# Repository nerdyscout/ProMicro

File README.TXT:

# ProMicro

## PCBs
collection of various PCBs stackable onto various MCU modules like
- [Sparkfun ProMicro](https://www.sparkfun.com/products/12587)
- [Arduino ProMini](https://store.arduino.cc/arduino-pro-mini)
- [Pro Mini nRF52](https://www.tindie.com/products/prominimicros/pro-mini-nrf52-nordic-nrf52832/)

:warning: all modules run with 3.3V, some might be 5V tolerant, but it is up to you to verify!

| PCB | Build | Status | Description |
| --- | --- | --- | --- |
| [ANA](ANA/README.TXT) |  | draft | 2ch analog in/out |
| [BOOST](BOOST) |  | prototype | Lipo battery charger |
| [BUS](BUS/README.TXT) |  | prototype | Modbus and CANbus module |
| [CONN](CONN/README.TXT) |  | prototype | CONN |
| [ESP](ESP) |  | draft | ESP |
| [LOG](LOG/README.TXT) |  | prototype | micro SD card shield with real time clock |
| [LORA](LORA/README.TXT) |  | prototype | Lora transceiver 868MHz |
| [POS](POS/README.TXT) |  | prototype | GPS receiver and gyroscope module |
| [QWIIC](QWIIC/README.TXT) |  | draft | BME280 sensor and analog extension |
| [UART](UART/README.TXT) |  | prototype | USB to RS232, RS485, SPI, I2C, JTAG |
| [WING](WING/README.TXT) |  | draft | Adafruit FeatherWing Breakout |
| [ZPM](ZPM/README.TXT) |  | draft | energy harvesting module |

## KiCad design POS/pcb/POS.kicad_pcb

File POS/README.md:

# ProMicro_POS 
This module can be mounted to an [Arduino Pro Mini](https://www.sparkfun.com/products/11113), [Arduino Nano](https://store.arduino.cc/arduino-nano), [Sparkfun Pro Micro](https://www.sparkfun.com/products/12587), or any other pincompatible MCU running with 3.3V. Depending on assembly it provides GPS and/or GYRO data. Manufacturing this PCB with 0.8mm thickness allows to mount a [LORA](../LORA) module onto its back.

## Documentation 
All files can be found on [Github](https://github.com/nerdyscout/ProMicro/tree/master/POS).

### Schematic

### BoM
  * [interactiveHTMLBoM](https://nerdyscout.github.io/ProMicro/POS/docs/bom/POS-ibom.html)
  * [octopart](pcb/docs/bom/POS-bom_octopart.csv)

## Hardware 
### Layout

### Gerbers
can be found within the Github [repository](pcb/gerbers).

## Code  (unless otherwise stated)
  * GPS
    * [Arduino Nano](examples/Arduino_Nano_GPS/Arduino_Nano_GPS.ino)
    * [Sparkfun ProMicro](examples/Sparkfun_GPS/Sparkfun_GPS.ino)
  * GYRO
    * [ICM20948](examples/Sparkfun_ICM20948/Sparkfun_ICM20948.ino)
    * [MPU9250](examples/Sparkfun_MPU9250/Sparkfun_MPU9250.ino)

## external
### Links
  * [hackaday.io](https://hackaday.io/project/171898-promicro)

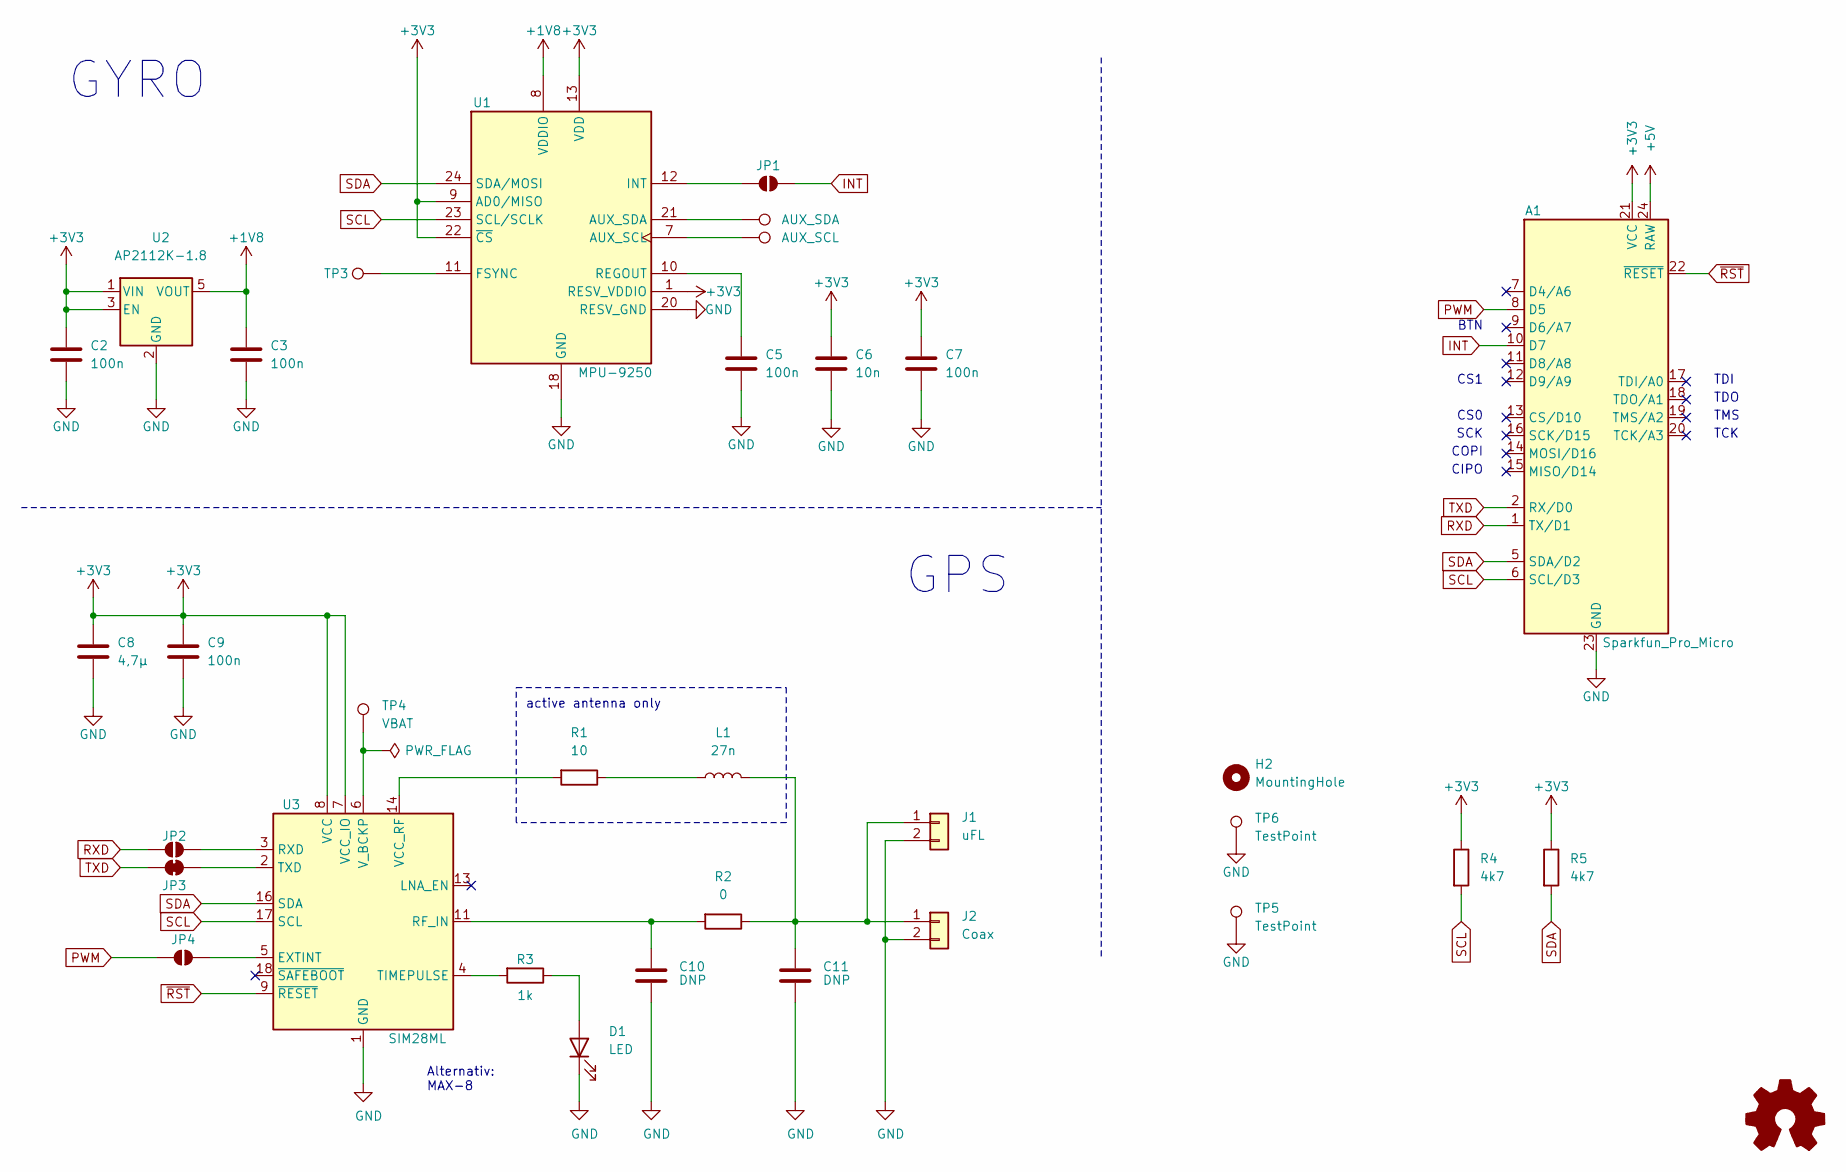
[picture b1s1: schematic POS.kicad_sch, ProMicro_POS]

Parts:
A1: Sparkfun_Pro_Micro
C2, C3, C5, C7, C9: 100n; C_0603_1608Metric; MPN CL05B104KO5NNNC; LCSC# C1525
C6: 10n; C_0603_1608Metric; MPN CL05B103KB5NNNC; LCSC# C15195
C8: 4,7µ; C_0603_1608Metric; MPN CL10A475KO8NNNC; LCSC# C19666
C10, C11: DNP; C_0603_1608Metric
D1: LED; LED_0603_1608Metric; MPN 19-217/BHC-ZL1M2RY/3T; LCSC# C72041
H2: MountingHole; MountingHole_2.1mm
J1: uFL; U.FL_Hirose_U.FL-R-SMT-1_Vertical
J2: Coax; SMA_Samtec_SMA-J-P-H-ST-EM1_EdgeMount
JP1, JP4: SolderJumper_2_Open; SolderJumper-2_P1.3mm_Open_RoundedPad1.0x1.5mm
JP2: Jumper_NO_Small; SolderJumper-2_P1.3mm_Open_RoundedPad1.0x1.5mm
JP3: Jumper_NC_Small; SolderJumper-2_P1.3mm_Bridged_RoundedPad1.0x1.5mm
L1: 27n; L_0603_1608Metric
LOGO1: Logo_Open_Hardware_Small; OSHW-Symbol_6.7x6mm_SilkScreen
R1: 10; R_0603_1608Metric
R2: 0; R_0603_1608Metric; MPN 0402WGF0000TCE; LCSC# C17168
R3: 1k; R_0603_1608Metric; MPN 0402WGF1001TCE; LCSC# C11702
R4, R5: 4k7; R_0603_1608Metric; MPN 0402WGF4701TCE; LCSC# C25900
TP1: AUX_SDA; TestPoint_Pad_D1.5mm
TP2: AUX_SCL; TestPoint_Pad_D1.5mm
TP3: FSYNC; TestPoint_Pad_D1.5mm
TP4: VBAT; TestPoint_THTPad_D1.5mm_Drill0.7mm
TP5, TP6: TestPoint; TestPoint_Pad_1.5x1.5mm
U1: MPU-9250; InvenSense_QFN-24_3x3mm_P0.4mm; MPN MPU-9250; LCSC# C71459
U2: AP2112K-1.8; SOT-23-5
U3: SIM28ML; ublox_MAX; MPN MAX-8C-0-10

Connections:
+1V8: C3.1, U1.8 (VDDIO), U2.5 (VOUT)
+3V3: A1.21 (VCC), C2.1, C6.1, C7.1, C8.1, C9.1, R4.1, R5.1, U1.1 (RESV_VDDIO), U1.9 (AD0/MISO), U1.13 (VDD), U1.22 (~CS), U2.1 (VIN), U2.3 (EN), U3.7 (VCC_IO), U3.8 (VCC)
+5V: A1.24 (RAW)
GND: A1.3 (GND), A1.4 (GND), A1.23 (GND), C2.2, C3.2, C5.2, C6.2, C7.2, C8.2, C9.2, C10.2, C11.2, D1.1 (K), J1.2, J2.2, TP5.1, TP6.1, U1.18 (GND), U1.20 (RESV_GND), U2.2 (GND), U3.1 (GND), U3.10 (GND), U3.12 (GND)
INT: A1.10 (D7), JP1.2 (B)
unnamed: C5.1, U1.10 (REGOUT)
unnamed: C10.1, R2.2, U3.11 (RF_IN)
unnamed: C11.1, J1.1, J2.1, L1.2, R2.1
unnamed: D1.2 (A), R3.1
unnamed: JP1.1 (A), U1.12 (INT)
unnamed: JP2.1 (A), U3.3 (RXD)
unnamed: JP3.1 (A), U3.2 (TXD)
unnamed: JP4.2 (B), U3.5 (EXTINT)
unnamed: L1.1, R1.1
unnamed: R1.2, U3.14 (VCC_RF)
unnamed: R3.2, U3.4 (TIMEPULSE)
unnamed: TP1.1, U1.21 (AUX_SDA)
unnamed: TP2.1, U1.7 (AUX_SCL)
unnamed: TP3.1, U1.11 (FSYNC)
unnamed: TP4.1, U3.6 (V_BCKP)
PWM: A1.8 (D5), JP4.1 (A)
RXD: A1.1 (TX/D1), JP2.2 (B)
SCL: A1.6 (SCL/D3), R4.2, U1.23 (SCL/SCLK), U3.17 (SCL)
SDA: A1.5 (SDA/D2), R5.2, U1.24 (SDA/MOSI), U3.16 (SDA)
TXD: A1.2 (RX/D0), JP3.2 (B)
~RST: A1.22 (~RESET), U3.9 (~RESET)

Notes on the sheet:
TMS
CIPO
CS1
TDI
GPS
TDO
BTN
GYRO
SCK
CS0
Alternativ: MAX-8
TCK
active antenna only
COPI

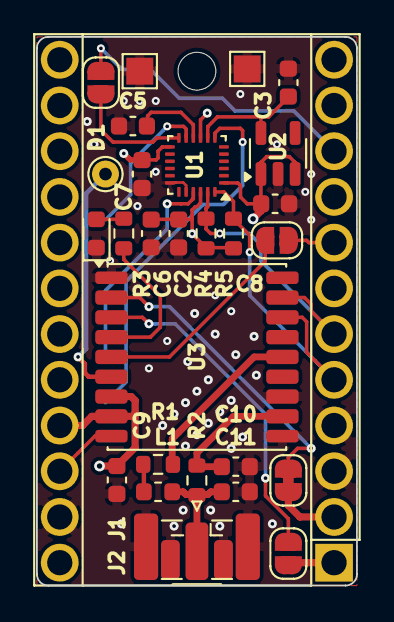
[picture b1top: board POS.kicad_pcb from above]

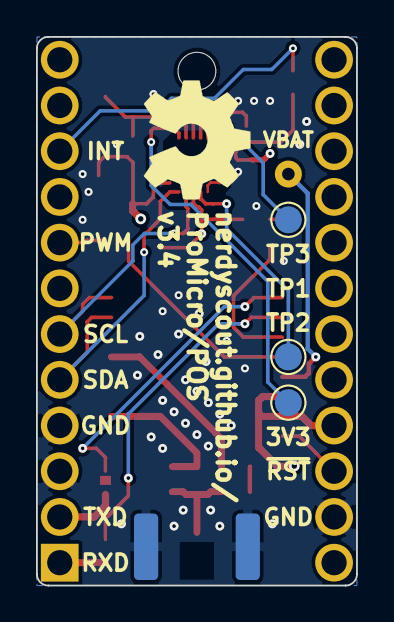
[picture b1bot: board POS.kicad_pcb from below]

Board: 4 copper layers, 17.8 x 30.5 mm, 34 parts (4 on the bottom side), 25 nets.

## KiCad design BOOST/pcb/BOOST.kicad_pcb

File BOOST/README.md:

# ProMicro_BOOST 
This module can be mounted, back on back, to any [Arduino Pro Mini](https://www.sparkfun.com/products/11113), [Arduino Nano](https://store.arduino.cc/arduino-nano) or [Sparkfun Pro Micro](https://www.sparkfun.com/products/12587) running with 3.3V. While the controller gets externally powered the BOOST battery is charging, removing the cable the device keeps running on battery.

## Documentation 
All files can be found on [Github](https://github.com/nerdyscout/ProMicro/tree/master/BOOST).

### Schematic

### BoM
  * [interactiveHTMLBoM](https://nerdyscout.github.io/ProMicro/BOOST/docs/bom/BOOST-ibom.html)
  * [octopart](pcb/docs/bom/BOOST-bom_octopart.csv)

## Hardware 
### Layout

### Gerbers
can be found within the Github [repository](pcb/gerbers).

## Code  (unless otherwise stated)
  * [readAnalog](examples/readAnalog/readAnalog.ino)

## external
### Links
  * [oshwa.org](https://certification.oshwa.org/de000102.html)
  * [hackaday.io](https://hackaday.io/project/171898-promicro)

### Credits
  * [Adafruit PowerBoost 500 Basic](https://learn.adafruit.com/adafruit-powerboost)

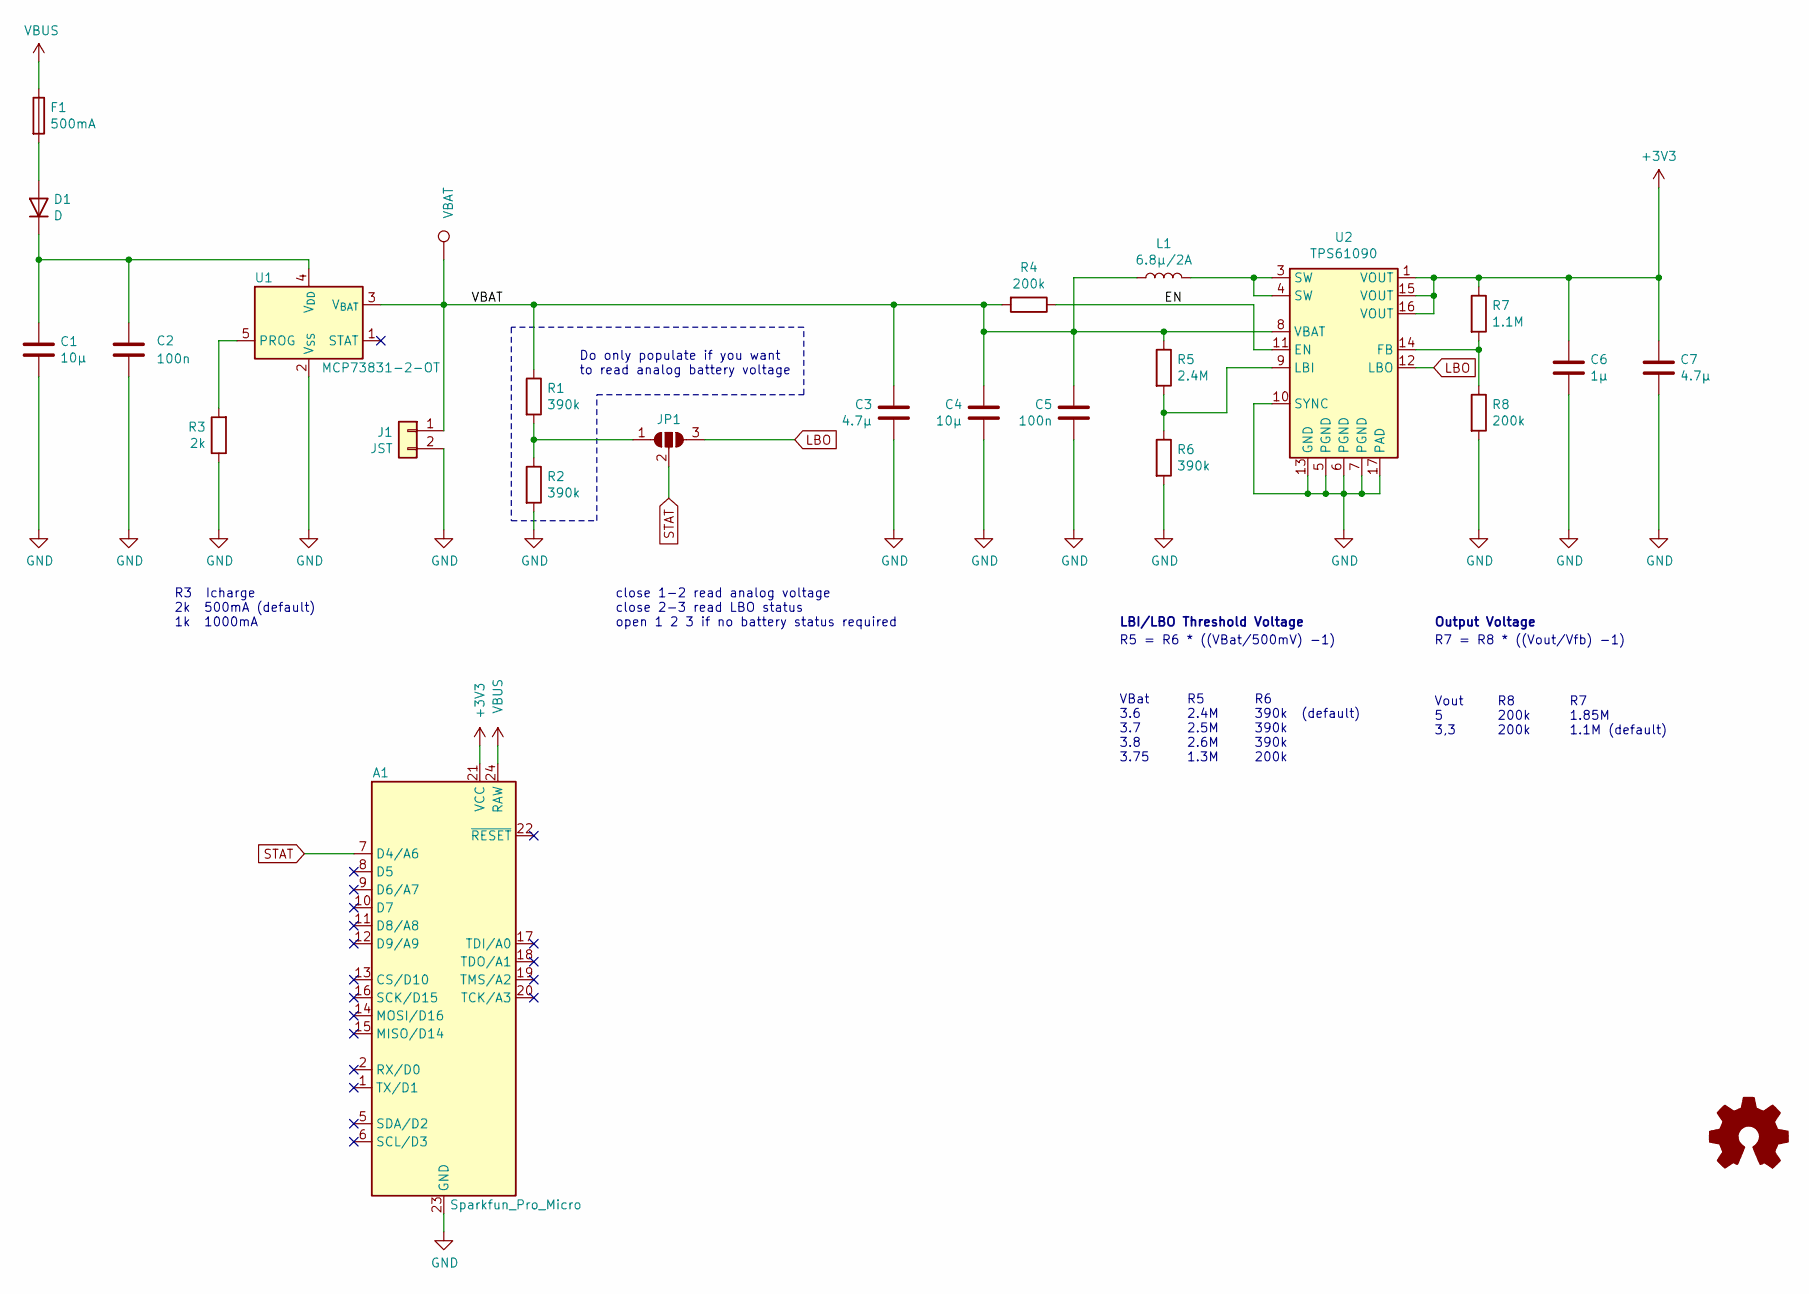
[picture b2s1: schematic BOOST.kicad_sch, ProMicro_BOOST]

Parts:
A1: Sparkfun_Pro_Micro
C1, C4: 10µ; C_0603_1608Metric; MPN CL10A106KP8NNNC
C2, C5: 100n; C_0603_1608Metric; MPN CL10B104KO8NNNC
C3, C7: 4.7µ; C_0603_1608Metric; MPN CL10A475KO8NNNC
C6: 1µ; C_0603_1608Metric; MPN C0603X105K9RACAUTO
D1: D; D_0603_1608Metric
F1: 500mA; Fuse_0603_1608Metric; MPN 04000025WR
J1: JST; JST_PH_S2B-PH-SM4-TB_1x02-1MP_P2.00mm_Horizontal
JP1: SolderJumper_3_Open; SolderJumper-3_P1.3mm_Open_RoundedPad1.0x1.5mm
L1: 6.8µ/2A; L_Bourns_SRN6045TA; MPN 744787068
LOGO1: Logo_Open_Hardware_Small; OSHW-Symbol_6.7x6mm_SilkScreen
R1, R2, R6: 390k; R_0603_1608Metric; MPN 0603WAF3903T5E
R3: 2k; R_0603_1608Metric; MPN 0603WAF2001T5E
R4, R8: 200k; R_0603_1608Metric; MPN 0603WAF2003T5E
R5: 2.4M; R_0603_1608Metric; MPN WR06W2404FTL
R7: 1.1M; R_0603_1608Metric; MPN RM06FTN1104
TP1: VBAT; TestPoint_THTPad_D2.0mm_Drill1.0mm
U1: MCP73831-2-OT; SOT-23-5; MPN MCP73831T-2ACI/OT
U2: TPS61090; Texas_RSA_VQFN-16-1EP_4x4mm_P0.65mm_EP2.7x2.7mm_ThermalVias; MPN TPS61090RSAR

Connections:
+3V3: A1.21 (VCC), C6.1, C7.1, R7.1, U2.1 (VOUT), U2.15 (VOUT), U2.16 (VOUT)
/EN: R4.1, U2.11 (EN)
/VBAT: C3.2, C4.2, C5.1, J1.1, L1.1, R1.1, R4.2, R5.1, TP1.1, U1.3 (V_{BAT}), U2.8 (VBAT)
GND: A1.3 (GND), A1.4 (GND), A1.23 (GND), C1.2, C2.1, C3.1, C4.1, C5.2, C6.2, C7.2, J1.2, R2.2, R3.1, R6.2, R8.2, U1.2 (V_{SS}), U2.5 (PGND), U2.6 (PGND), U2.7 (PGND), U2.10 (SYNC), U2.13 (GND), U2.17 (PAD)
LBO: JP1.3 (B), U2.12 (LBO)
unnamed: D1.2 (A), F1.2
unnamed: C1.1, C2.2, D1.1 (K), U1.4 (V_{DD})
unnamed: JP1.1 (A), R1.2, R2.1
unnamed: L1.2, U2.3 (SW), U2.4 (SW)
unnamed: R3.2, U1.5 (PROG)
unnamed: R7.2, R8.1, U2.14 (FB)
unnamed: R5.2, R6.1, U2.9 (LBI)
STAT: A1.7 (D4/A6), JP1.2 (C)
VBUS: A1.24 (RAW), F1.1

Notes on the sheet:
R7 1.85M 1.1M (default)
Vout 5 3,3
LBI/LBO Threshold Voltage
Output Voltage
R7 = R8 * ((Vout/Vfb) -1)
R6 390k (default) 390k 390k 200k
close 1-2 read analog voltage close 2-3 read LBO status open 1 2 3 if no battery status required
R3 Icharge 2k 500mA (default) 1k 1000mA
Do only populate if you want to read analog battery voltage
R5 = R6 * ((VBat/500mV) -1)
R5 2.4M 2.5M 2.6M 1.3M
VBat 3.6 3.7 3.8 3.75
R8 200k 200k

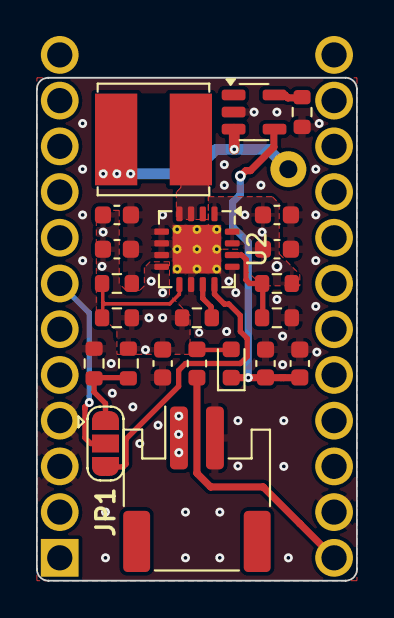
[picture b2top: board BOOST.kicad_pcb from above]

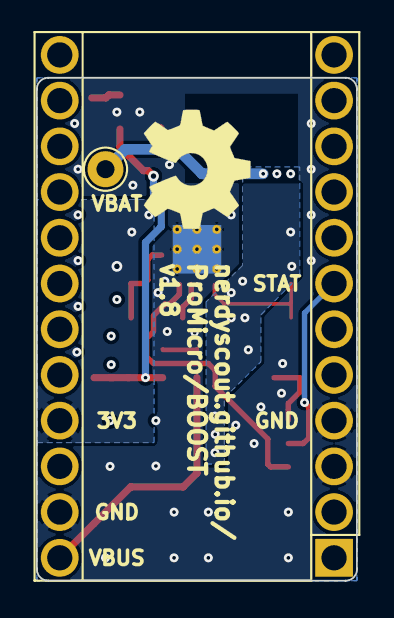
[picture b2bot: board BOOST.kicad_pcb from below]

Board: 4 copper layers, 17.8 x 27.9 mm, 25 parts (3 on the bottom side), 14 nets.

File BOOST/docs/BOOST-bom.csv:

References;Description;Part;Value;Qty;mpn;variant
C2 C5;Unpolarized capacitor;C;100n;2;CL10B104KO8NNNC;3V3, 5V
C6;Unpolarized capacitor;C;1µ;1;C0603X105K9RACAUTO;
C3 C7;Unpolarized capacitor;C;4.7µ;2;CL10A475KO8NNNC;
C1 C4;Unpolarized capacitor;C;10µ;2;CL10A106KP8NNNC;3V3, 5V
D1;Diode;D;D;1;;3V3, 5V
F1;Fuse;Fuse;500mA;1;04000025WR;
J1;Generic connector, single row, 01x02, script generated (kicad-library-utils/schlib/autogen/connector/);Conn_01x02;JST;1;;3V3, 5V
L1;Inductor;L;6.8µ/2A;1;744787068;
R3;Resistor;R;2k;1;0603WAF2001T5E;
R4 R8;Resistor;R;200k;2;0603WAF2003T5E;
R1 R2 R6;Resistor;R;390k;3;0603WAF3903T5E;
R7;Resistor;R;1.1M;1;RM06FTN1104;
R5;Resistor;R;2.4M;1;WR06W2404FTL;
U1;Single cell, Li-Ion/Li-Po charge management controller, 4.20V, Tri-State Status Output, in SOT23-5 package;MCP73831-2-OT;MCP73831-2-OT;1;MCP73831T-2ACI/OT;3V3, 5V
U2;2A Step-Up DC-DC Converter for Batteries, Isw up to 2500mA, Adjustable output voltage, QFN-16;TPS61090;TPS61090;1;TPS61090RSAR;3V3, 5V

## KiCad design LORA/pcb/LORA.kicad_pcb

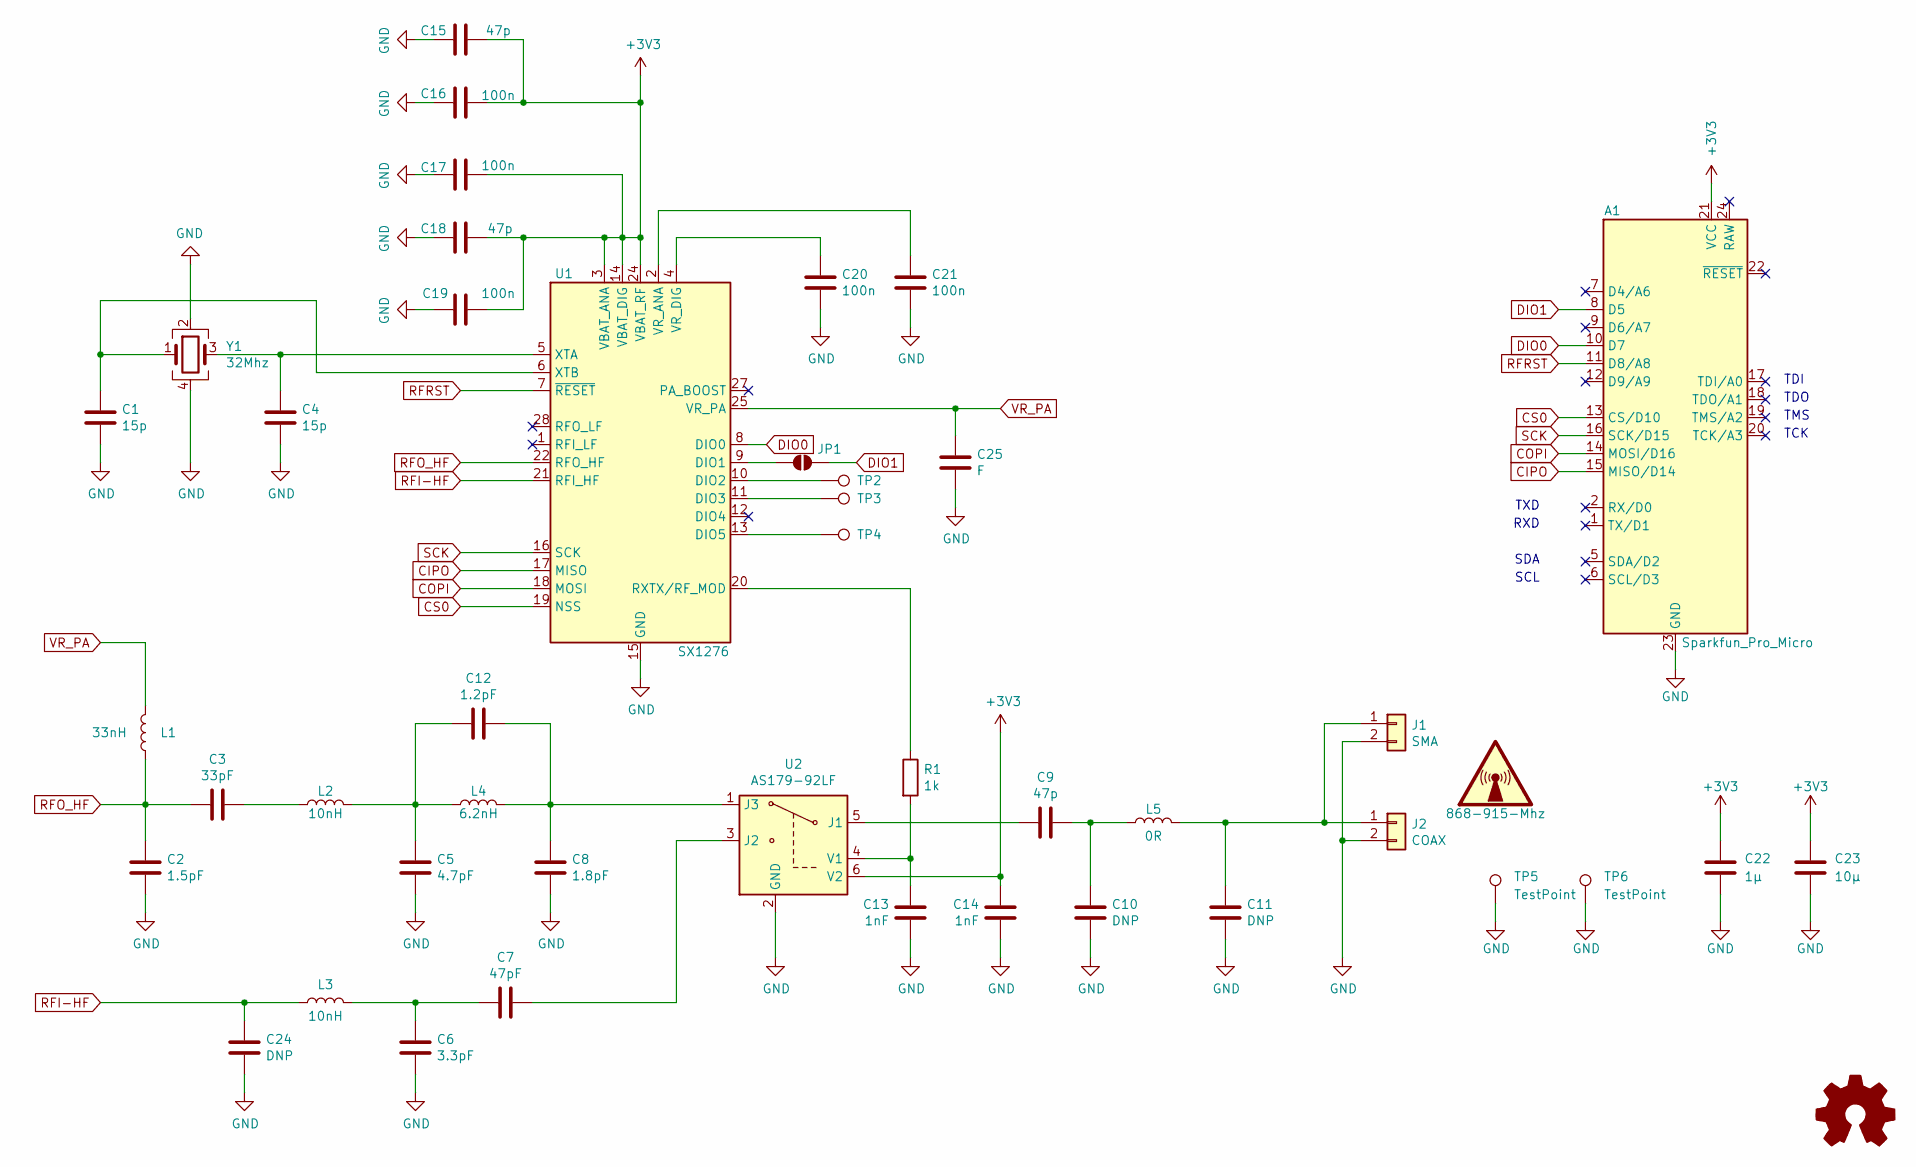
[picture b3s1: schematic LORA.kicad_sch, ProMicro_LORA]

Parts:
A1: Sparkfun_Pro_Micro
C1, C4: 15p; C_0402_1005Metric; MPN 0402CG150J500NT; LCSC# C1548
C2: 1.5pF; C_0402_1005Metric; MPN 0402CG1R5C500NT; LCSC# C1552
C3: 33pF; C_0402_1005Metric; MPN 0402CG330J500NT; LCSC# C1562
C5: 4.7pF; C_0402_1005Metric; MPN 0402CG4R7C500NT; LCSC# C1569
C6: 3.3pF; C_0402_1005Metric; MPN 0402CG3R3C500NT; LCSC# C1565
C7: 47pF; C_0402_1005Metric; MPN 0402CG470J500NT; LCSC# C1567
C8: 1.8pF; C_0402_1005Metric
C9, C15, C18: 47p; C_0402_1005Metric; MPN 0402CG470J500NT; LCSC# C1567
C10, C11, C24: DNP; C_0402_1005Metric
C12: 1.2pF; C_0402_1005Metric; MPN CL05C1R2BB5NNNC; LCSC# C159809
C13, C14: 1nF; C_0402_1005Metric; MPN 0402B102K500NT; LCSC# C1523
C16, C17, C19, C20, C21: 100n; C_0402_1005Metric; MPN CL05B104KO5NNNC; LCSC# C1525
C22: 1µ; C_0402_1005Metric; MPN CL05A105KA5NQNC; LCSC# C52923
C23: 10µ; C_0603_1608Metric; MPN CL05A106MQ5NUNC; LCSC# C15525
C25: F; C_0402_1005Metric
J1: SMA; U.FL_Hirose_U.FL-R-SMT-1_Vertical
J2: COAX; SMA_Samtec_SMA-J-P-H-ST-EM1_EdgeMount
JP1: SolderJumper_2_Open; SolderJumper-2_P1.3mm_Open_RoundedPad1.0x1.5mm
L1: 33nH; L_0402_1005Metric; MPN HK100533NJ-T; LCSC# C87193
L2, L3: 10nH; L_0402_1005Metric; MPN SDCL1005C10NJTDF; LCSC# C27147
L4: 6.2nH; L_0402_1005Metric; MPN MLG1005S6N2ST000; LCSC# C87534
L5: 0R; L_0402_1005Metric; MPN 0402WGF0000TCE; LCSC# C17168
LOGO1: Logo_Open_Hardware_Small; OSHW-Symbol_6.7x6mm_SilkScreen
R1: 1k; R_0402_1005Metric; MPN 0402WGF1001TCE; LCSC# C11702
TP2: DIO2; TestPoint_Pad_D1.0mm
TP3: DIO3; TestPoint_Pad_D1.0mm
TP4: DIO5; TestPoint_Pad_D1.0mm
TP5, TP6: TestPoint; TestPoint_Pad_1.5x1.5mm
U1: SX1276; QFN-28-1EP_6x6mm_P0.65mm_EP4.8x4.8mm
U2: AS179-92LF; SOT-363_SC-70-6; MPN AS179-92LF; LCSC# C83422
Y1: 32Mhz; Crystal_SMD_SeikoEpson_FA238V-4Pin_3.2x2.5mm; MPN X1E000021016300; LCSC# C91742

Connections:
+3V3: A1.21 (VCC), C14.1, C15.1, C16.2, C17.2, C18.1, C19.2, C22.1, C23.1, U1.3 (VBAT_ANA), U1.14 (VBAT_DIG), U1.24 (VBAT_RF), U2.6 (V2)
CIPO: A1.15 (MISO/D14), U1.17 (MISO)
COPI: A1.14 (MOSI/D16), U1.18 (MOSI)
CS0: A1.13 (CS/D10), U1.19 (NSS)
DIO0: A1.10 (D7), U1.8 (DIO0)
DIO1: A1.8 (D5), JP1.2 (B)
GND: A1.3 (GND), A1.4 (GND), A1.23 (GND), C1.2, C2.1, C4.2, C5.2, C6.2, C8.2, C10.2, C11.2, C13.2, C14.2, C15.2, C16.1, C17.1, C18.2, C19.1, C20.2, C21.2, C22.2, C23.2, C24.2, C25.2, J1.2, J2.2, TP5.1, TP6.1, U1.15 (GND), U1.23 (GND), U1.26 (GND), U1.29 (GND), U2.2 (GND), Y1.2, Y1.4
unnamed: C3.1, L2.1
unnamed: C6.1, C7.2, L3.2
unnamed: C9.1, C10.1, L5.1
unnamed: C5.1, C12.2, L2.2, L4.1
unnamed: C11.1, J1.1, J2.1, L5.2
unnamed: JP1.1 (A), U1.9 (DIO1)
unnamed: TP2.1, U1.10 (DIO2)
unnamed: TP3.1, U1.11 (DIO3)
unnamed: TP4.1, U1.13 (DIO5)
unnamed: R1.1, U1.20 (RXTX/RF_MOD)
unnamed: C21.1, U1.2 (VR_ANA)
unnamed: C20.1, U1.4 (VR_DIG)
unnamed: C4.1, U1.5 (XTA), Y1.3
unnamed: C1.1, U1.6 (XTB), Y1.1
unnamed: C9.2, U2.5 (J1)
unnamed: C7.1, U2.3 (J2)
unnamed: C8.1, C12.1, L4.2, U2.1 (J3)
unnamed: C13.1, R1.2, U2.4 (V1)
RFI-HF: C24.1, L3.1, U1.21 (RFI_HF)
RFO_HF: C2.2, C3.2, L1.1, U1.22 (RFO_HF)
RFRST: A1.11 (D8/A8), U1.7 (~RESET)
SCK: A1.16 (SCK/D15), U1.16 (SCK)
VR_PA: C25.1, L1.2, U1.25 (VR_PA)

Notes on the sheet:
TDI
TCK
SDA
SCL
TXD
RXD
TDO
TMS

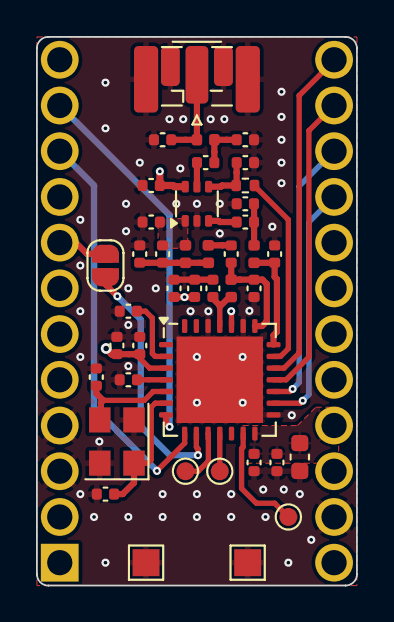
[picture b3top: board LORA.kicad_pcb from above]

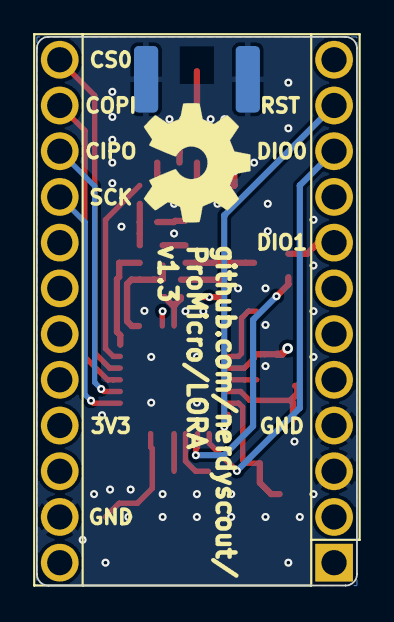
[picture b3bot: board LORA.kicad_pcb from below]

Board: 4 copper layers, 17.8 x 30.5 mm, 44 parts (2 on the bottom side), 30 nets.

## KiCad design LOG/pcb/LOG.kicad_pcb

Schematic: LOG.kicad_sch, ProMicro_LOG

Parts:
A1: Sparkfun_Pro_Micro
C1: 100n; C_0603_1608Metric
D1: LED; LED_0603_1608Metric
J1: Micro_SD_Card_Det; microSD_HC_Molex_104031-0811
JP1, JP2: Jumper_NO_Small; SolderJumper-2_P1.3mm_Open_RoundedPad1.0x1.5mm
JP3: SolderJumper_3_Bridged12; SolderJumper-3_P1.3mm_Bridged12_RoundedPad1.0x1.5mm_NumberL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
LOGO1: Logo_Open_Hardware_Small; OSHW-Symbol_6.7x6mm_SilkScreen
R1, R2, R3, R5, R6: 4k7; R_0603_1608Metric
R4: 1k; R_0603_1608Metric
TP1: VBAT; TestPoint_THTPad_D2.0mm_Drill1.0mm
U1: DS3231MZ; SOIC-8_3.9x4.9mm_P1.27mm

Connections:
+3V3: A1.21 (VCC), C1.1, J1.4, R2.1, R3.1, R5.1, R6.1, U1.2 (VCC)
BTN: A1.9 (D6/A7), R1.2
CIPO: A1.15 (MISO/D14), J1.7
COPI: A1.14 (MOSI/D16), J1.3
CS: J1.2, JP3.2 (C)
CS0: A1.13 (CS/D10), JP3.3 (B)
CS1: A1.12 (D9/A9), JP3.1 (A)
GND: A1.3 (GND), A1.4 (GND), A1.23 (GND), C1.2, D1.1 (K), J1.6, J1.10, J1.11, U1.5 (GND)
INT: A1.10 (D7), JP2.2 (B)
unnamed: D1.2 (A), R4.2
unnamed: J1.9, R1.1
unnamed: JP1.1 (A), R3.2, U1.1 (32KHZ)
unnamed: JP2.1 (A), R2.2, U1.3 (~INT/SQW)
unnamed: TP1.1, U1.6 (VBAT)
PWM: A1.8 (D5), JP1.2 (B)
SCK: A1.16 (SCK/D15), J1.5, R4.1
SCL: A1.6 (SCL/D3), R5.2, U1.8 (SCL)
SDA: A1.5 (SDA/D2), R6.2, U1.7 (SDA)
~RST: A1.22 (~RESET), U1.4 (~RST)

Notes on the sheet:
TDI
TD0
TMS
TCK

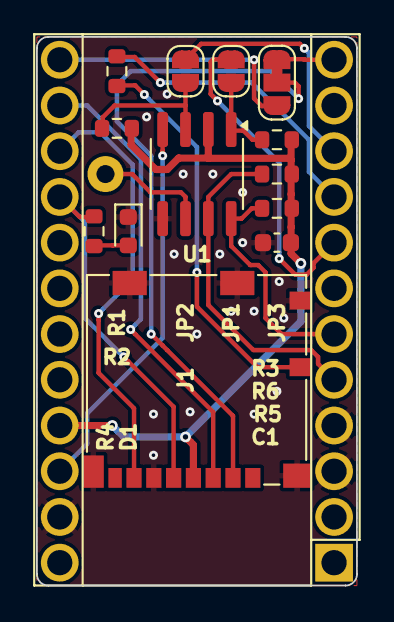
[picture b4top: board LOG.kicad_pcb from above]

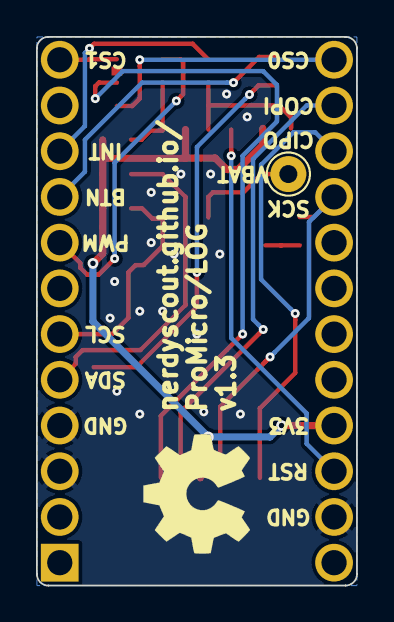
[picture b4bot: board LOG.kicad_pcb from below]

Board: 2 copper layers, 17.8 x 30.5 mm, 16 parts (2 on the bottom side), 19 nets.

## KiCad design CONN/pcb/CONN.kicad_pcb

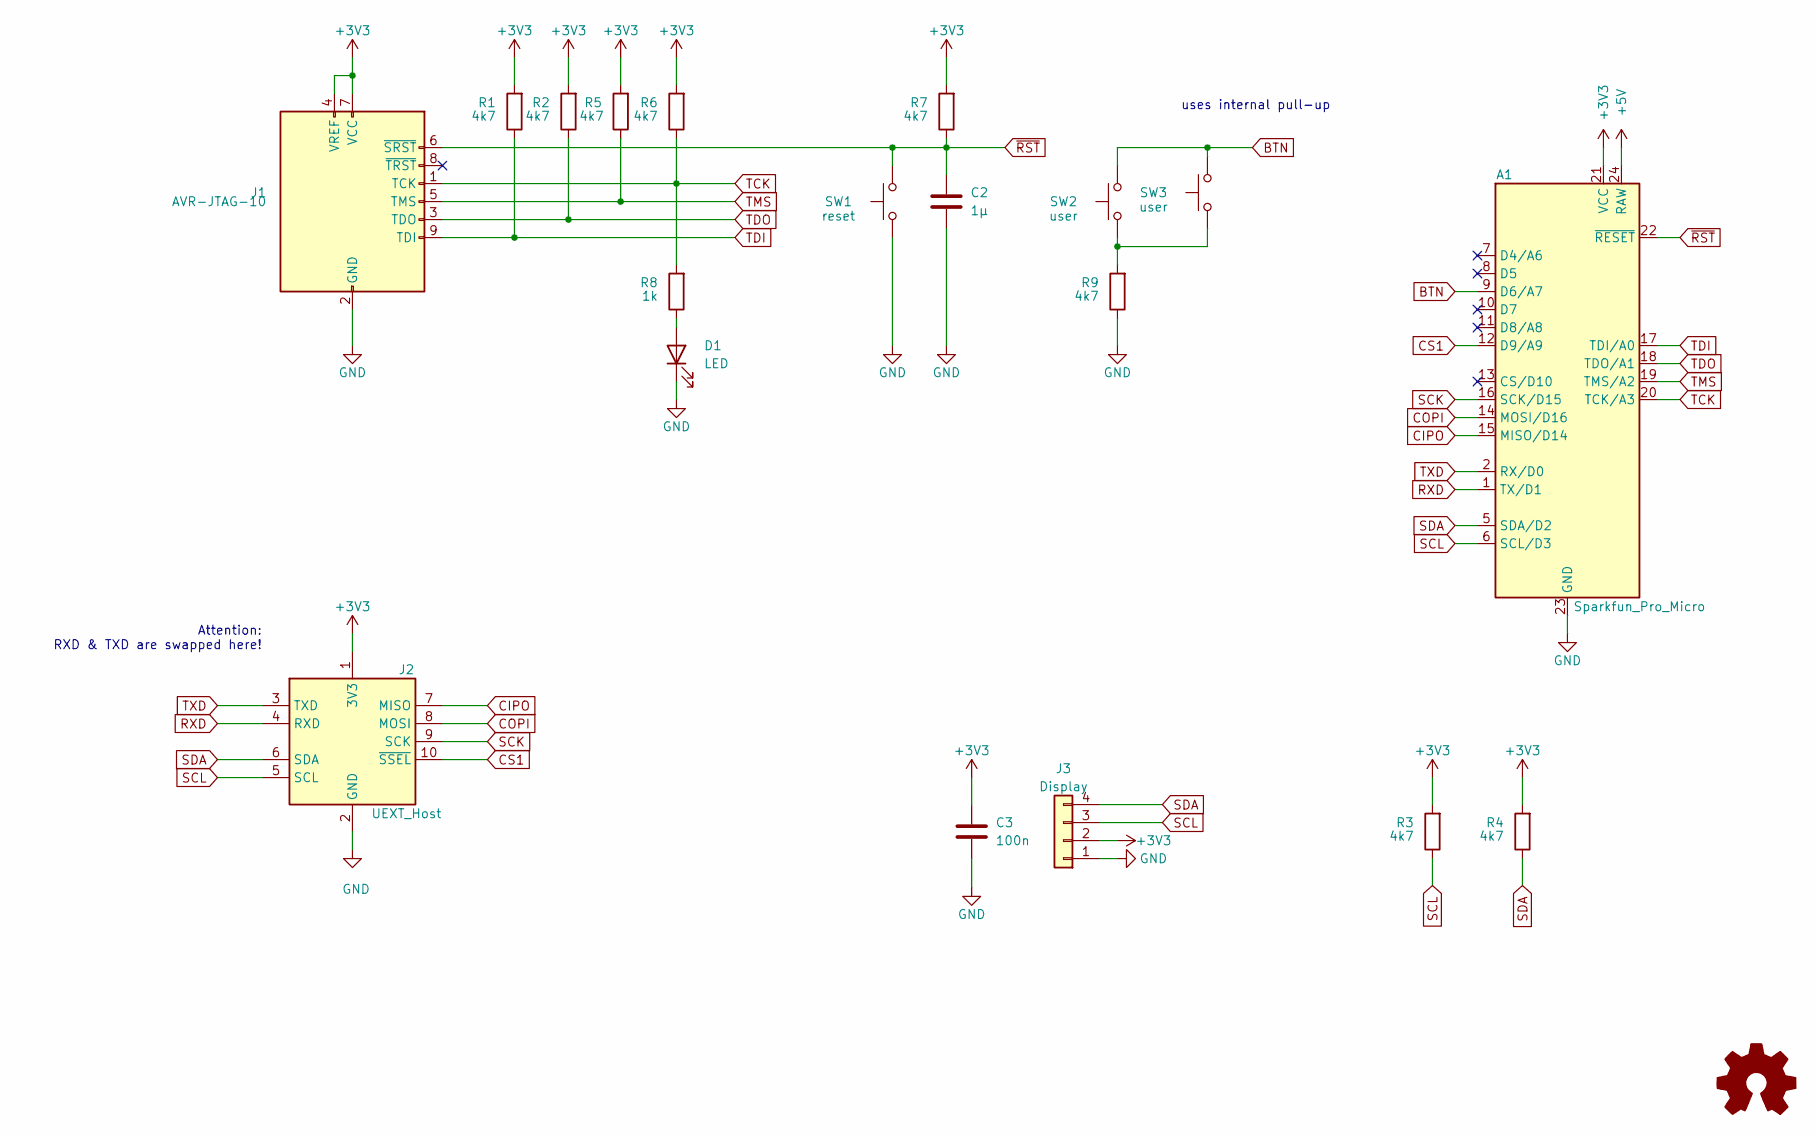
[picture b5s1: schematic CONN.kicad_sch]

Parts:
A1: Sparkfun_Pro_Micro
C2: 1µ; C_0603_1608Metric; MPN CL10A105KB8NNNC; LCSC# C15849
C3: 100n; C_0603_1608Metric; MPN CC0603KRX7R9BB104; LCSC# C14663
D1: LED; LED_0603_1608Metric; MPN 19-217/GHC-YR1S2/3T; LCSC# C72043
J1: AVR-JTAG-10; IDC-Header_2x05_P2.54mm_Vertical
J2: UEXT_Host; UEXT
J3: Display; PinHeader_1x04_P2.54mm_Vertical
LOGO1: Logo_Open_Hardware_Small; OSHW-Symbol_6.7x6mm_SilkScreen
R1, R2, R3, R4, R5, R6, R7, R9: 4k7; R_0603_1608Metric; MPN 0603WAF4701T5E; LCSC# C23162
R8: 1k; R_0603_1608Metric
SW1: reset; SW_SPST_B3U-1000P; MPN B3U-1000P
SW2: user; SW_SPST_B3U-1000P; MPN B3U-1000P
SW3: user; SW_SPST_CK_RS282G05A3; MPN B3U-1000P

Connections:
+3V3: A1.21 (VCC), C3.1, J1.4 (VREF), J1.7 (VCC), J2.1 (3V3), J3.2, R1.2, R2.2, R3.2, R4.2, R5.2, R6.2, R7.2
+5V: A1.24 (RAW)
BTN: A1.9 (D6/A7), SW2.2, SW3.2
CIPO: A1.15 (MISO/D14), J2.7 (MISO)
COPI: A1.14 (MOSI/D16), J2.8 (MOSI)
CS1: A1.12 (D9/A9), J2.10 (~SSEL)
GND: A1.3 (GND), A1.4 (GND), A1.23 (GND), C2.2, C3.2, D1.1 (K), J1.2 (GND), J1.10 (GND), J2.2 (GND), J3.1, R9.1, SW1.1
unnamed: D1.2 (A), R8.1
unnamed: R9.2, SW2.1, SW3.1
RXD: A1.1 (TX/D1), J2.4 (RXD)
SCK: A1.16 (SCK/D15), J2.9 (SCK)
SCL: A1.6 (SCL/D3), J2.5 (SCL), J3.3, R3.1
SDA: A1.5 (SDA/D2), J2.6 (SDA), J3.4, R4.1
TCK: A1.20 (TCK/A3), J1.1 (TCK), R6.1, R8.2
TDI: A1.17 (TDI/A0), J1.9 (TDI), R1.1
TDO: A1.18 (TDO/A1), J1.3 (TDO), R2.1
TMS: A1.19 (TMS/A2), J1.5 (TMS), R5.1
TXD: A1.2 (RX/D0), J2.3 (TXD)
~RST: A1.22 (~RESET), C2.1, J1.6 (~SRST), R7.1, SW1.2

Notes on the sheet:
uses internal pull-up
Attention: RXD & TXD are swapped here!

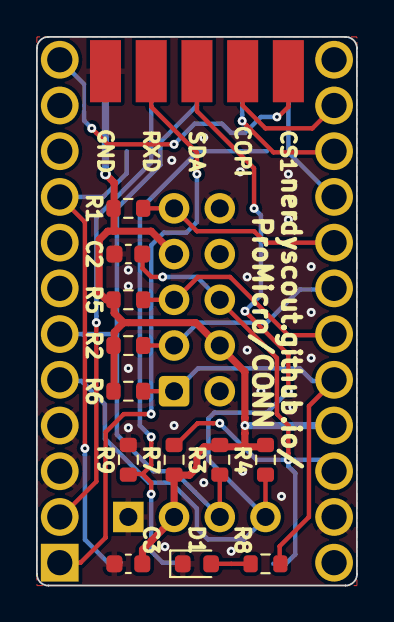
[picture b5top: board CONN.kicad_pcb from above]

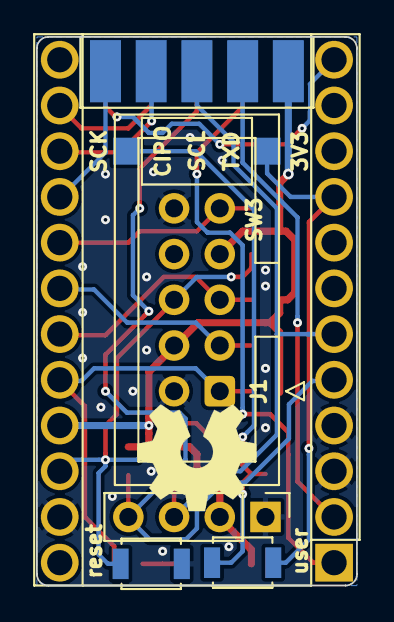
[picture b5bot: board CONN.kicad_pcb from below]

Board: 4 copper layers, 17.8 x 30.5 mm, 20 parts (8 on the bottom side), 18 nets.

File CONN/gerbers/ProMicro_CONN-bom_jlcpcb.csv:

Comment,Designator,Package,lcsc#,mpn
Sparkfun_Pro_Micro,A1,Sparkfun_Pro_Micro,,
100n,C3,C_0603_1608Metric,C14663,CC0603KRX7R9BB104
1µ,C2,C_0603_1608Metric,C15849,CL10A105KB8NNNC
LED,D1,LED_0603_1608Metric,C72043,19-217/GHC-YR1S2/3T
AVR-JTAG-10,J1,IDC-Header_2x05_P2.54mm_Vertical,,
Display,J3,PinHeader_1x04_P2.54mm_Vertical,,
UEXT_Host,J2,UEXT,,
Logo_Open_Hardware_Small,LOGO1,OSHW-Symbol_6.7x6mm_SilkScreen,,
1k,R8,R_0603_1608Metric,,
4k7,R1,R_0603_1608Metric,C23162,0603WAF4701T5E
4k7,R2,R_0603_1608Metric,C23162,0603WAF4701T5E
4k7,R3,R_0603_1608Metric,C23162,0603WAF4701T5E
4k7,R4,R_0603_1608Metric,C23162,0603WAF4701T5E
4k7,R5,R_0603_1608Metric,C23162,0603WAF4701T5E
4k7,R6,R_0603_1608Metric,C23162,0603WAF4701T5E
4k7,R7,R_0603_1608Metric,C23162,0603WAF4701T5E
4k7,R9,R_0603_1608Metric,C23162,0603WAF4701T5E
reset,SW1,SW_SPST_B3U-1000P,,B3U-1000P
user,SW2,SW_SPST_B3U-1000P,,B3U-1000P

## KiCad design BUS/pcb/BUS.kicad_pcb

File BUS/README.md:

# ProMicro_BUS
This module can be mounted to an [Arduino Pro Mini](https://www.sparkfun.com/products/11113), [Arduino Nano](https://store.arduino.cc/arduino-nano), [Sparkfun Pro Micro](https://www.sparkfun.com/products/12587), or any other pincompatible MCU running with 3.3V. Depending on assembly it provides a RTC and/or µSD card slot.

## Documentation 
All files can be found on [Github](https://github.com/nerdyscout/ProMicro/tree/master/BUS).

### Schematic

### BoM
  * [interactiveHTMLBoM](https://nerdyscout.github.io/ProMicro/BUS/docs/bom/BUS-ibom.html)
  * [octopart](pcb/docs/bom/BUS-bom_octopart.csv)

## Hardware 
### Layout

### Gerbers
can be found within the Github [repository](pcb/gerbers).

## Code  (unless otherwise stated)
  * Modbus
    * [Modbus1](examples/Modbus1/Modbus1.ino)
  * Canbus
    * [Canbus1](examples/Canbus1/Canbus1.ino)

## external
### Links
  * [hackaday.io](https://hackaday.io/project/171898-promicro)

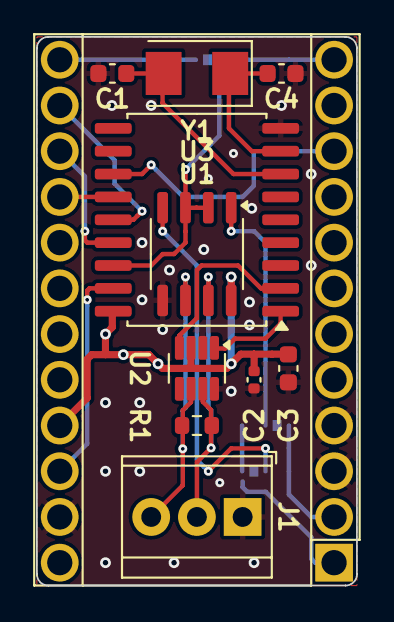
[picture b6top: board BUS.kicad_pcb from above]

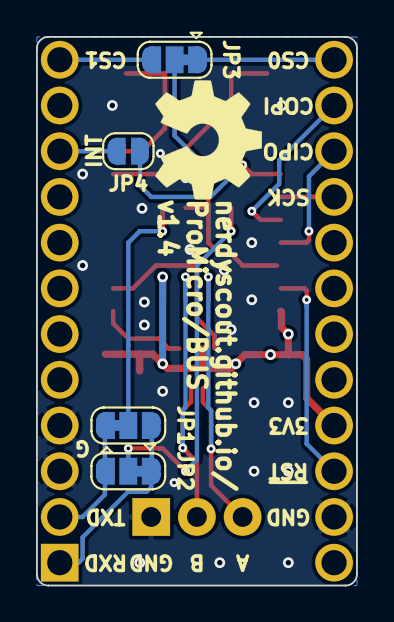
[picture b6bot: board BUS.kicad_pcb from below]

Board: 2 copper layers, 17.8 x 30.5 mm, 16 parts (5 on the bottom side), 21 nets.

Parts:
A1: Sparkfun_Pro_Micro
C1, C4: C; C_0603_1608Metric
C2: 100n; C_0402_1005Metric
C3: 10µ; C_0603_1608Metric
J1: Conn_01x03; TerminalBlock_TE_282834-3_1x03_P2.54mm_Horizontal
JP1, JP2, JP3: SolderJumper_3_Bridged12; SolderJumper-3_P1.3mm_Bridged12_RoundedPad1.0x1.5mm
JP4: SolderJumper_2_Open; SolderJumper-2_P1.3mm_Open_RoundedPad1.0x1.5mm
LOGO1: Logo_Open_Hardware_Small; OSHW-Symbol_6.7x6mm_SilkScreen
R1: 120; R_0603_1608Metric
U1: MAX3483; SO-8_3.9x4.9mm_P1.27mm
U2: MAX3051; SOT-23-8
U3: MCP2515-xSO; SOIC-18W_7.5x11.6mm_P1.27mm
Y1: Crystal; Crystal_SMD_5032-2Pin_5.0x3.2mm

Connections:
+3V3: A1.21, C2.1, C3.1, U1.8, U2.3, U3.18
/A: J1.3, R1.2, U1.6, U2.6
/B: J1.2, R1.1, U1.7, U2.7
CIPO: A1.15, U3.15
COPI: A1.14, U3.14
CS: JP3.2, U1.2, U1.3, U3.16
CS0: A1.13, JP3.1
CS1: A1.12, JP3.3
GND: A1.3, A1.4, A1.23, C1.1, C2.2, C3.2, C4.2, J1.1, U1.5, U2.2, U2.8, U3.9
INT: A1.10, JP4.2
unnamed: C1.2, U3.7, Y1.2
unnamed: C4.1, U3.8, Y1.1
unnamed: JP1.2, U1.1
unnamed: JP2.2, U1.4
unnamed: JP4.1, U3.12
unnamed: U2.1, U3.1
unnamed: U2.4, U3.2
RXD: A1.1, JP1.3, JP2.1
SCK: A1.16, U3.13
TXD: A1.2, JP1.1, JP2.3
~RST: A1.22, U3.17

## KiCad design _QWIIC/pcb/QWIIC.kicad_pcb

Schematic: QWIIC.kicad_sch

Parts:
A1: Sparkfun_Pro_Micro_3V3; Sparkfun_Pro_Micro
C1: 10µ; C_0603_1608Metric
C2, C3, C4: 100n; C_0603_1608Metric
J1, J2: Qwiic; JST_SH_BM04B-SRSS-TB_1x04-1MP_P1.00mm_Vertical
J3, J4: Conn_01x02; PinHeader_1x02_P2.54mm_Vertical
J5, J6: Conn_01x03; PinHeader_1x03_P2.54mm_Vertical
JP1, JP2, JP3: SolderJumper_3_Bridged12; SolderJumper-3_P1.3mm_Bridged12_RoundedPad1.0x1.5mm
LOGO1: Logo_Open_Hardware_Small; OSHW-Symbol_6.7x6mm_SilkScreen
R3: 4k7; R_0603_1608Metric; MPN RC0402FR-074K7L
R4: 4k7; R_0603_1608Metric; MPN RC0402FR-074K7L; lcsc# C105871
U1: ADS1015IDGS; TSSOP-10_3x3mm_P0.5mm
U2: BME280; Bosch_LGA-8_2.5x2.5mm_P0.65mm_ClockwisePinNumbering

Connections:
+3V3: A1.21, C1.1, C2.1, C3.1, J1.2, J2.2, J5.3, J6.3, JP3.1 (A), R3.2, R4.2, U2.2 (CSB), U2.5 (SDO), U2.6 (VDDIO), U2.8 (VDD)
+5V: A1.24, JP3.3 (B)
/LIPO_VBAT: J3.2, U1.4 (AIN0)
A2: A1.19, J5.2, JP2.3 (B), U1.6 (AIN2)
A3: A1.20, J6.2, JP1.3 (B), U1.7 (AIN3)
GND: A1.4, A1.23, C1.2, C2.2, C3.2, C4.2, J1.1, J2.1, J5.1, J6.1, U1.3 (GND), U2.1 (GND), U2.7 (GND)
unnamed: C4.1, JP3.2 (C), U1.8 (VDD)
unnamed: J3.1, U1.5 (AIN1)
unnamed: J4.1, JP1.2 (C)
unnamed: J4.2, JP2.2 (C)
SCL: A1.6, J1.4, J2.4, JP1.1 (A), R3.1, U1.10 (SCL), U2.4 (SCK)
SDA: A1.5, J1.3, J2.3, JP2.1 (A), R4.1, U1.9 (SDA), U2.3 (SDI)

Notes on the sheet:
TDI
TMS
CS0
VBAT/2
CS1
TDO
TCK
INT
BTN

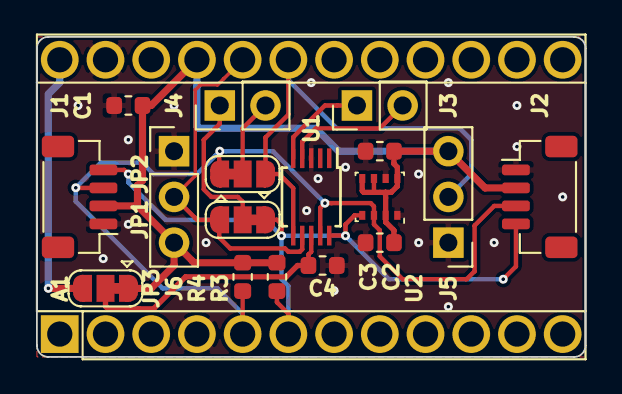
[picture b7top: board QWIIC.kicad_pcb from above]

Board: 2 copper layers, 30.5 x 17.8 mm, 19 parts (1 on the bottom side), 12 nets.

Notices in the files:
BOOST/README.md:
Documentation [![CC BY-SA](../img/ccbysa.png)](pcb/docs/LICENSE.TXT):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
BOOST/pcb/BOOST.kicad_pcb:
CERN-OHL-S-2.0
